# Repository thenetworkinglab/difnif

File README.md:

# DifNif: DBA-ESDI Solid State Drive Emulator

DifNif is a drive emulator that replaces an IBM DBA-ESDI hard drive. 
It was designed by Eric Schlaepfer ([schlae/difnif](https://github.com/schlae/difnif)),
with the project's initial release intended to replace the hard drive in 
IBM ThinkPad 700C laptops, also including an alpha version of a PS/2 desktop 
form-factor emulator.  This fork is an attempt to complete 
the development of the 72-pin board for PS/2 desktops; the changes are 
listed in [docs/formfactor-review.md](docs/formfactor-review.md).

And before you ask: the name 'DifNif' comes from DF9F, 
the Micro Channel adapter ID that IBM's DBA-ESDI drives report.

**Status: alpha.** See "Status" below before building anything.

## Background

IBM PS/2 computers from the late 1980s and early 1990s typically used a
disk interface called DBA-ESDI (Direct Bus Attach - Enhanced
Small Device Interface). A DBA-ESDI drive has its controller integrated
with the drive electronics, and sits directly on the Micro Channel
bus, more like an IDE drive, but with its own register interface.

These drives are becoming rare because many have failed mechanically or
been damaged by leaking capacitors. MCA SCSI cards are an alternative on some
machines, but are getting expensive and difficult to find as well and 
aren't compatible with all PS/2s. Some PS/2s also need an IML (initial microcode load)
partition on their disk, and can only load it from a DBA-ESDI drive.

DifNif uses a Teensy 4.1 microcontroller and a Lattice iCE40 FPGA to implement the
DBA-ESDI interface, and stores the disk as an image file on an SD card. 

## Two boards, one design

The boards share the FPGA design (`verilog/`) and the Teensy firmware
(`difnift/`), and differ in how they connect to the computer.

| | ThinkPad board | PS/2 desktop board |
|---|---|---|
| Folder | [pcb_thinkpad](pcb_thinkpad/) | [pcb_formfactor](pcb_formfactor/) |
| Machines | ThinkPad 700C | PS/2 desktops that take a 72-pin DBA-ESDI drive, such as the 50Z, 55SX and 70 |
| Connector | 2 mm header, wired to the flex cable taken from a stock 700-series 2.5" drive | 72-pin (2 x 36) card edge, plugging straight into the drive socket |
| Carrier | [mech/df9f_carrier.STL](mech/df9f_carrier.STL) | [mech/difnif_PS2_drive_sled.STL](mech/difnif_PS2_drive_sled.STL), replacing the IBM drive sled |
| FPGA build | `make` | `make BOARD=ps2` |

There are also debugging aids:

- [pcb_finglonger](pcb_finglonger/), the "Fing Longer", for the ThinkPad board.
  It fits a 3D-printed sled ([mech/finglong.STL](mech/finglong.STL)) held by two
  clips ([mech/2finglong.STL](mech/2finglong.STL)). One acts as an extender
  that brings the connector forward, and a second as a breakout for logic
  analyzer probes on the bus lines.
- For the 72-pin board, a card in a spare Micro Channel slot gives access to
  the bus signals; Eric used a spare
  [Snark Barker MCA](https://github.com/schlae/snark-barker-mca).

## Status

- **ThinkPad board:** Eric's board works in a ThinkPad 700C,
  running Windows 3.1. The FPGA design has since been changed in this fork (see
  [docs/formfactor-review.md](docs/formfactor-review.md)), and those changes
  have **not** been tested on a ThinkPad. Eric's original files are on the
  `main` branch.
- **PS/2 desktop board, Rev P1** (Eric's): register communication didn't work
  reliably in a 50Z.
- **PS/2 desktop board, Rev P2** (this fork): fixes the problems found in a
  review of Rev P1, including a floating reset input that is the likely cause
  of the 50Z problem. The fixes have been checked in simulation against IBM's
  bus timing, but **Rev P2 has not yet been built or tested on real hardware.**
- Both boards' original design powers the 74LVC4245A level shifters the wrong
  way round, putting 5V on a supply pin rated for 4.6V at most. Rev P2 uses
  the TI SN74LVC8T245 instead, which accepts 5V on either side and fits the
  same footprint. The same swap should work on the ThinkPad board but hasn't
  been tried.
- Known bugs: writes occasionally produce a sector shifted by one byte; the
  cause hasn't been found.

[docs/formfactor-review.md](docs/formfactor-review.md) has the full list of
findings and changes, and [docs/verify-findings.md](docs/verify-findings.md)
explains how to check each one against Eric's original files and IBM's
documents.

**Data loss:** this is a hobby project with no formal testing. Keep backup
copies of all disk images.

## Building

This is an advanced project. It needs surface-mount soldering (or an
assembly service), two programmable devices to load, and probably debugging
with an oscilloscope and a logic analyzer.

### Boards

Each board folder has a `fab/` folder with Gerber and drill files. For the
Rev P2 PS/2 board, `pcb_formfactor/fab/` also has a parts list
(`DifNifFormFactor-RevP2-BOM.csv`) and a placement file
(`DifNifFormFactor-RevP2-positions.csv`) for an assembly service. The
ordering notes in [docs/formfactor-review.md](docs/formfactor-review.md)
cover board thickness, gold fingers and the bevelled edge.

The Teensy 4.1 plugs into two 24-pin female header strips (2.54 mm pitch, rows
15.24 mm apart). The SD card goes in the Teensy's own card slot.

### Teensy firmware

Load [difnift/difnift.ino](difnift/difnift.ino) with the Arduino IDE and
PJRC's Teensy board support, selecting Teensy 4.1.

For register loopback testing with DIFDIAG, comment out the two lines at the
start of `loop()` that call `esdiReset()` and `mainLoop()`. The serial monitor
then accepts the single-letter test commands listed at startup.

### FPGA

The FPGA design is built with the open-source iCE40 tools (yosys, nextpnr and
icestorm, for example from
[oss-cad-suite](https://github.com/YosysHQ/oss-cad-suite-build)). In
`verilog/`:

    make                  # ThinkPad board
    make BOARD=ps2        # PS/2 desktop board

The PS/2 build turns on the POS registers, so the card reports its `DF9F`
ID. Each build goes into its own folder, `build/thinkpad/` or `build/ps2/`.

The FPGA loads its program from an SPI flash chip on the board, which is
written through header J2 with an FTDI FT232H or FT2232H adapter and
`iceprog`:

    make prog BOARD=ps2

| J2 pin | Signal | FT232H pin |
|---|---|---|
| 1 | Flash chip select | AD4 |
| 2 | CDONE | AD6 |
| 3 | SCK | AD0 |
| 4 | CRESET | AD7 |
| 5 | Flash data out (CIPO) | AD2 |
| 6 | GND | GND |
| 7 | Flash data in (COPI) | AD1 |
| 8 | +3.3 V (board supply, leave unconnected) | |

The board must be powered while programming. The Teensy's USB connection can
power it on the bench.

The source files are:

- `difnif_top.v`: top level, wiring up the other modules.
- `mcabus.v`: the Micro Channel bus interface, with the ESDI registers, POS
  registers and DMA.
- `teensy.v`: the register interface that lets the Teensy, in its own clock
  domain, reach the ESDI mailbox registers and flags.

The self-checking bus simulation for the PS/2 board is `difnif72_t.v`, run with
`./run_sim72.sh` (needs Icarus Verilog).

## Drive images

The Teensy firmware uses a file called `disk0.img` in the root of the SD card.
Its size must be a whole number of megabytes, up to 1023 MB; for example, for
120 MB:

    dd if=/dev/zero of=disk0.img bs=1048576 count=120

Then use the machine's reference disk to create the IML and reference
partitions, and install DOS to partition and format the rest of the disk.

## DIFDIAG

[difdiag/DIFDIAG.CPP](difdiag/DIFDIAG.CPP) is a diagnostic utility for
DBA-ESDI drives that works directly with the drive hardware at a very low
level. Don't use it on drives containing data you care about, but it can help
with troubleshooting dead drives. It compiles with Borland C++ using the Large
memory model.

Menus:

- **Settings:** DMA configuration. Autoconfigure tries to get the DMA channel
  through a BIOS call, and failing that from the extended BIOS data area
  (EBDA). The channel can also be set by hand, or PIO mode chosen instead.
- **Mailbox tests:** not for real drives. With DifNif in loopback test mode
  (see "Teensy firmware"), runs millions of register cycles to look for timing
  problems.
- **Low level commands:** the lowest-level commands, which must be run in the
  sequence given by the flowcharts in the
  [ESDI spec](https://ardent-tool.com/docs/pdf/j_mcspec.pdf).
- **Drive information:** query commands; generally safe on real drives.
- **POST tests:** modelled on the drive tests run by the PS/2 BIOS.
- **Run diagnostics:** the DBA-ESDI interface's own low-level hardware
  diagnostic command.
- **Int13 tests:** destructive. Writes data through the BIOS int13 routines,
  reads it back and compares.
- **Read sector:** reads one or more sectors and shows them in hex.

## Reference documents

- [IBM DBA-ESDI reference](https://ardent-tool.com/docs/pdf/j_mcspec.pdf)
- [DBA-ESDI 72-pin connector pinout](https://ardent-tool.com/storage/DBA_ESDI.html)
- [IBM PS/2 Hardware Interface Technical Reference, Micro Channel chapter](https://ardent-tool.com/docs/pdf/ps2_50-60_techref_ch2_microchannel_architecture.pdf)

## License

Designed by Eric Schlaepfer; modified in this fork by thenetworkinglab (2026).
Licensed under the
[CERN Open Hardware Licence Version 2 - Strongly Reciprocal](https://ohwr.org/cern_ohl_s_v2.txt).

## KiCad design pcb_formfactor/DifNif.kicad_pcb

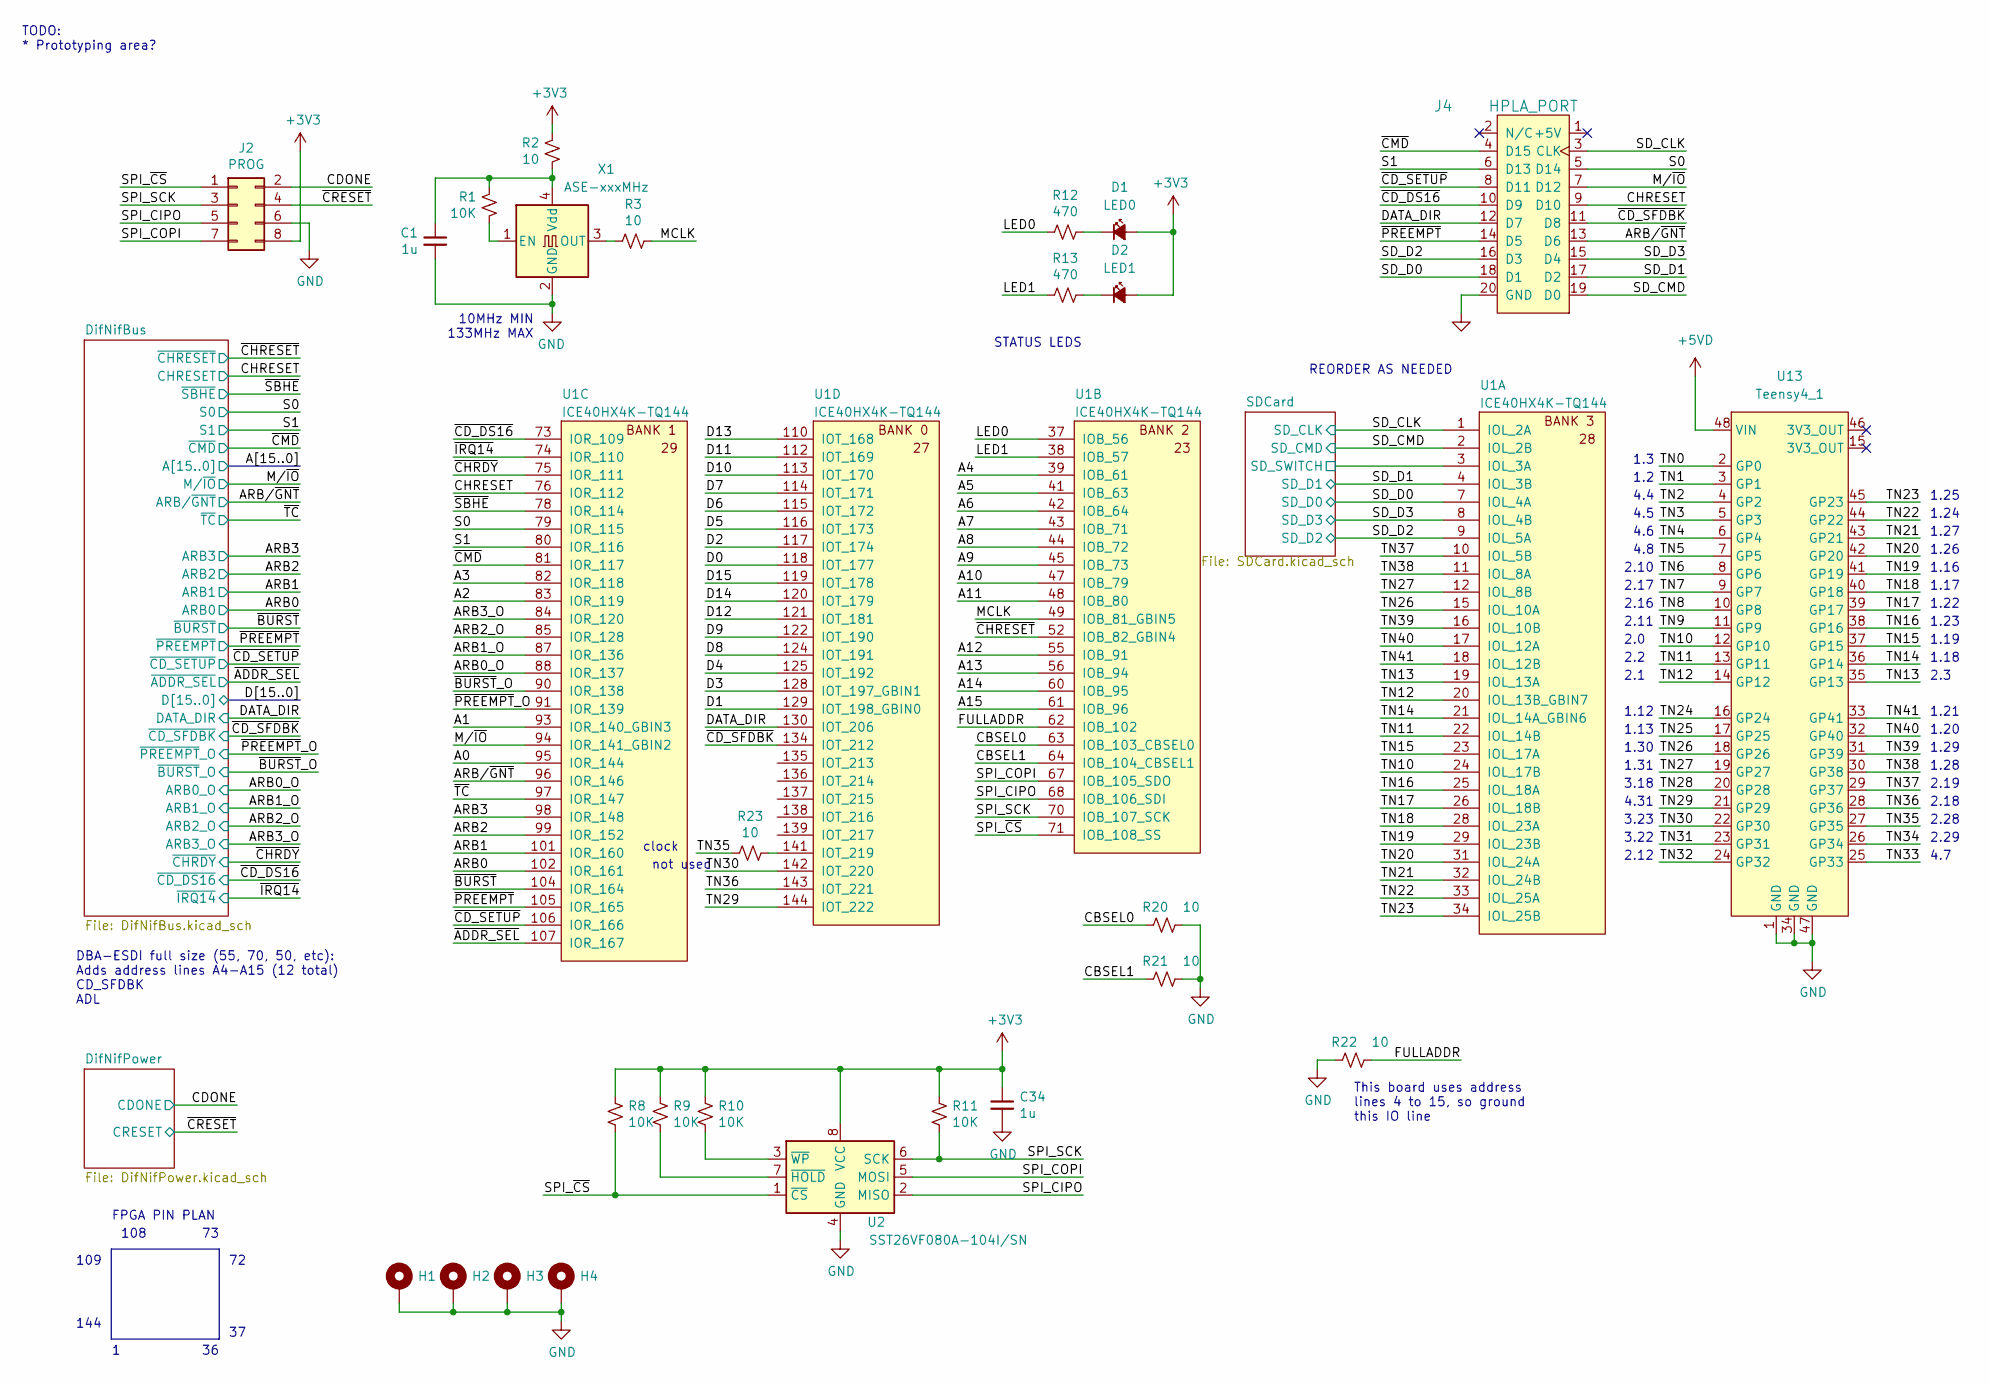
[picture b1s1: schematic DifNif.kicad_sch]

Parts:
C1, C34: 1u; CAPC1608X100; Mouser 810-CGA3E1X7R1C105AC
D1: LED0; LEDM1608X50
D2: LED1; LEDM1608X50
H1, H2, H3, H4: MountingHole_Pad; MountingHole_2.7mm_Pad
J2: PROG; PinHeader_2x04_P2.54mm_Vertical
J4: HPLA_PORT; PinHeader_2x10_P2.54mm_Vertical
R1, R8, R9, R10, R11: 10K; RESC1608X55; Mouser 603-RC0603FR-0710KL
R2, R3, R20, R21, R22, R23: 10; RESC1608X55; Mouser 603-RC0603FR-0710RL
R12, R13: 470; RESC1608X55; Mouser 603-RC0603FR-07470RL
U1: ICE40HX4K-TQ144; TSQFP50P2200X2200X160-144; Mouser 842-ICE40HX4K-TQ144
U2: SST26VF080A-104I/SN; SOP127P620X175-8; Mouser 579-26VF080A-104I/SN
U13: Teensy4_1; DIP-48_W15.24mm_Socket
X1: ASE-xxxMHz; XTAL320X250X120-4; Mouser 520-ECS-2333-100-BNT

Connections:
+3V3: C34.1, D1.2 (A), D2.2 (A), J2.8, R2.1, R8.1, R9.1, R10.1, R11.1, U2.8 (VCC); also elsewhere on the board
+5VD: U13.48 (VIN); also elsewhere on the board
/A0: U1.95 (IOR_144); also elsewhere on the board
/A1: U1.93 (IOR_140_GBIN3); also elsewhere on the board
/A2: U1.83 (IOR_119); also elsewhere on the board
/A3: U1.82 (IOR_118); also elsewhere on the board
/A4: U1.39 (IOB_61); also elsewhere on the board
/A5: U1.41 (IOB_63); also elsewhere on the board
/A6: U1.42 (IOB_64); also elsewhere on the board
/A7: U1.43 (IOB_71); also elsewhere on the board
/A8: U1.44 (IOB_72); also elsewhere on the board
/A9: U1.45 (IOB_73); also elsewhere on the board
/A10: U1.47 (IOB_79); also elsewhere on the board
/A11: U1.48 (IOB_80); also elsewhere on the board
/A12: U1.55 (IOB_91); also elsewhere on the board
/A13: U1.56 (IOB_94); also elsewhere on the board
/A14: U1.60 (IOB_95); also elsewhere on the board
/A15: U1.61 (IOB_96); also elsewhere on the board
/ARB0: U1.102 (IOR_161); also elsewhere on the board
/ARB0_O: U1.88 (IOR_137); also elsewhere on the board
/ARB1: U1.101 (IOR_160); also elsewhere on the board
/ARB1_O: U1.87 (IOR_136); also elsewhere on the board
/ARB2: U1.99 (IOR_152); also elsewhere on the board
/ARB2_O: U1.85 (IOR_128); also elsewhere on the board
/ARB3: U1.98 (IOR_148); also elsewhere on the board
/ARB3_O: U1.84 (IOR_120); also elsewhere on the board
/ARB/~GNT: J4.13 (D6), U1.96 (IOR_146); also elsewhere on the board
/CBSEL0: R20.2, U1.63 (IOB_103_CBSEL0)
/CBSEL1: R21.2, U1.64 (IOB_104_CBSEL1)
/CDONE: J2.2; also elsewhere on the board
/CHRESET: J4.9 (D10), U1.76 (IOR_112); also elsewhere on the board
/D0: U1.118 (IOT_177); also elsewhere on the board
/D1: U1.129 (IOT_198_GBIN0); also elsewhere on the board
/D2: U1.117 (IOT_174); also elsewhere on the board
/D3: U1.128 (IOT_197_GBIN1); also elsewhere on the board
/D4: U1.125 (IOT_192); also elsewhere on the board
/D5: U1.116 (IOT_173); also elsewhere on the board
/D6: U1.115 (IOT_172); also elsewhere on the board
/D7: U1.114 (IOT_171); also elsewhere on the board
/D8: U1.124 (IOT_191); also elsewhere on the board
/D9: U1.122 (IOT_190); also elsewhere on the board
/D10: U1.113 (IOT_170); also elsewhere on the board
/D11: U1.112 (IOT_169); also elsewhere on the board
/D12: U1.121 (IOT_181); also elsewhere on the board
/D13: U1.110 (IOT_168); also elsewhere on the board
/D14: U1.120 (IOT_179); also elsewhere on the board
/D15: U1.119 (IOT_178); also elsewhere on the board
/DATA_DIR: J4.12 (D7), U1.130 (IOT_206); also elsewhere on the board
/FULLADDR: R22.1, U1.62 (IOB_102)
/LED0: R12.2, U1.37 (IOB_56)
/LED1: R13.2, U1.38 (IOB_57)
/MCLK: R3.1, U1.49 (IOB_81_GBIN5)
/M/~IO: J4.7 (D12), U1.94 (IOR_141_GBIN2); also elsewhere on the board
/S0: J4.5 (D14), U1.79 (IOR_115); also elsewhere on the board
/S1: J4.6 (D13), U1.80 (IOR_116); also elsewhere on the board
/SDCard/SD_SWITCH: U1.3 (IOL_3A); also elsewhere on the board
/SD_CLK: J4.3 (CLK), U1.1 (IOL_2A); also elsewhere on the board
/SD_CMD: J4.19 (D0), U1.2 (IOL_2B); also elsewhere on the board
/SD_D0: J4.18 (D1), U1.7 (IOL_4A); also elsewhere on the board
/SD_D1: J4.17 (D2), U1.4 (IOL_3B); also elsewhere on the board
/SD_D2: J4.16 (D3), U1.9 (IOL_5A); also elsewhere on the board
/SD_D3: J4.15 (D4), U1.8 (IOL_4B); also elsewhere on the board
/SPI_CIPO: J2.5, U1.68 (IOB_106_SDI), U2.2 (MISO)
/SPI_COPI: J2.7, U1.67 (IOB_105_SDO), U2.5 (MOSI)
/SPI_SCK: J2.3, R11.2, U1.70 (IOB_107_SCK), U2.6 (SCK)
/SPI_~CS: J2.1, R8.2, U1.71 (IOB_108_SS), U2.1 (~CS)
/TN0: U13.2 (GP0)
/TN1: U13.3 (GP1)
/TN2: U13.4 (GP2)
/TN3: U13.5 (GP3)
/TN4: U13.6 (GP4)
/TN5: U13.7 (GP5)
/TN6: U13.8 (GP6)
/TN7: U13.9 (GP7)
/TN8: U13.10 (GP8)
/TN9: U13.11 (GP9)
/TN10: U1.24 (IOL_17B), U13.12 (GP10)
/TN11: U1.22 (IOL_14B), U13.13 (GP11)
/TN12: U1.20 (IOL_13B_GBIN7), U13.14 (GP12)
/TN13: U1.19 (IOL_13A), U13.35 (GP13)
/TN14: U1.21 (IOL_14A_GBIN6), U13.36 (GP14)
/TN15: U1.23 (IOL_17A), U13.37 (GP15)
/TN16: U1.25 (IOL_18A), U13.38 (GP16)
/TN17: U1.26 (IOL_18B), U13.39 (GP17)
/TN18: U1.28 (IOL_23A), U13.40 (GP18)
/TN19: U1.29 (IOL_23B), U13.41 (GP19)
/TN20: U1.31 (IOL_24A), U13.42 (GP20)
/TN21: U1.32 (IOL_24B), U13.43 (GP21)
/TN22: U1.33 (IOL_25A), U13.44 (GP22)
/TN23: U1.34 (IOL_25B), U13.45 (GP23)
/TN24: U13.16 (GP24)
/TN25: U13.17 (GP25)
/TN26: U1.15 (IOL_10A), U13.18 (GP26)
/TN27: U1.12 (IOL_8B), U13.19 (GP27)
/TN28: U13.20 (GP28)
/TN29: U1.144 (IOT_222), U13.21 (GP29)
/TN30: U1.142 (IOT_220), U13.22 (GP30)
/TN31: U13.23 (GP31)
/TN32: U13.24 (GP32)
/TN33: U13.25 (GP33)
/TN34: U13.26 (GP34)
/TN35: R23.2, U13.27 (GP35)
/TN36: U1.143 (IOT_221), U13.28 (GP36)
/TN37: U1.10 (IOL_5B), U13.29 (GP37)
/TN38: U1.11 (IOL_8A), U13.30 (GP38)
/TN39: U1.16 (IOL_10B), U13.31 (GP39)
/TN40: U1.17 (IOL_12A), U13.32 (GP40)
/TN41: U1.18 (IOL_12B), U13.33 (GP41)
/~ADDR_SEL: U1.107 (IOR_167)
/~BURST: U1.104 (IOR_164); also elsewhere on the board
/~BURST_O: U1.90 (IOR_138); also elsewhere on the board
/~CD_DS16: J4.10 (D9), U1.73 (IOR_109); also elsewhere on the board
/~CD_SETUP: J4.8 (D11), U1.106 (IOR_166); also elsewhere on the board
/~CD_SFDBK: J4.11 (D8), U1.134 (IOT_212); also elsewhere on the board
/~CHRDY: U1.75 (IOR_111); also elsewhere on the board
/~CHRESET: U1.52 (IOB_82_GBIN4); also elsewhere on the board
/~CMD: J4.4 (D15), U1.81 (IOR_117); also elsewhere on the board
/~CRESET: J2.4; also elsewhere on the board
/~IRQ14: U1.74 (IOR_110); also elsewhere on the board
/~PREEMPT: J4.14 (D5), U1.105 (IOR_165); also elsewhere on the board
/~PREEMPT_O: U1.91 (IOR_139); also elsewhere on the board
/~SBHE: U1.78 (IOR_114); also elsewhere on the board
/~TC: U1.97 (IOR_147); also elsewhere on the board
GND: C1.2, C34.2, H1.1, H2.1, H3.1, H4.1, J2.6, J4.20 (GND), R20.1, R21.1, R22.2, U2.4 (GND), U13.1 (GND), U13.34 (GND), U13.47 (GND), X1.2 (GND); also elsewhere on the board
unnamed: D1.1 (K), R12.1
unnamed: D2.1 (K), R13.1
unnamed: R23.1, U1.141 (IOT_219)
unnamed: R9.2, U2.7 (~HOLD)
unnamed: R10.2, U2.3 (~WP)
unnamed: R1.2, X1.1 (EN)
unnamed: R3.2, X1.3 (OUT)
unnamed: C1.1, R1.1, R2.2, X1.4 (Vdd)

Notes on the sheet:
2.1
2.19
4.31
1.16
2.17
2.18
1.30
2.16
1.27
clock
1.2
REORDER AS NEEDED
2.3
2.0
3.22
STATUS LEDS
TODO: * Prototyping area?
4.7
1.31
1.21
2.28
1.24
1.29
1.19
4.6
2.12
2.10
3.18
1.17
3.23
1.3
1.25
4.5
1.20
2.29
2.11
4.4
1.18
1.28
2.2

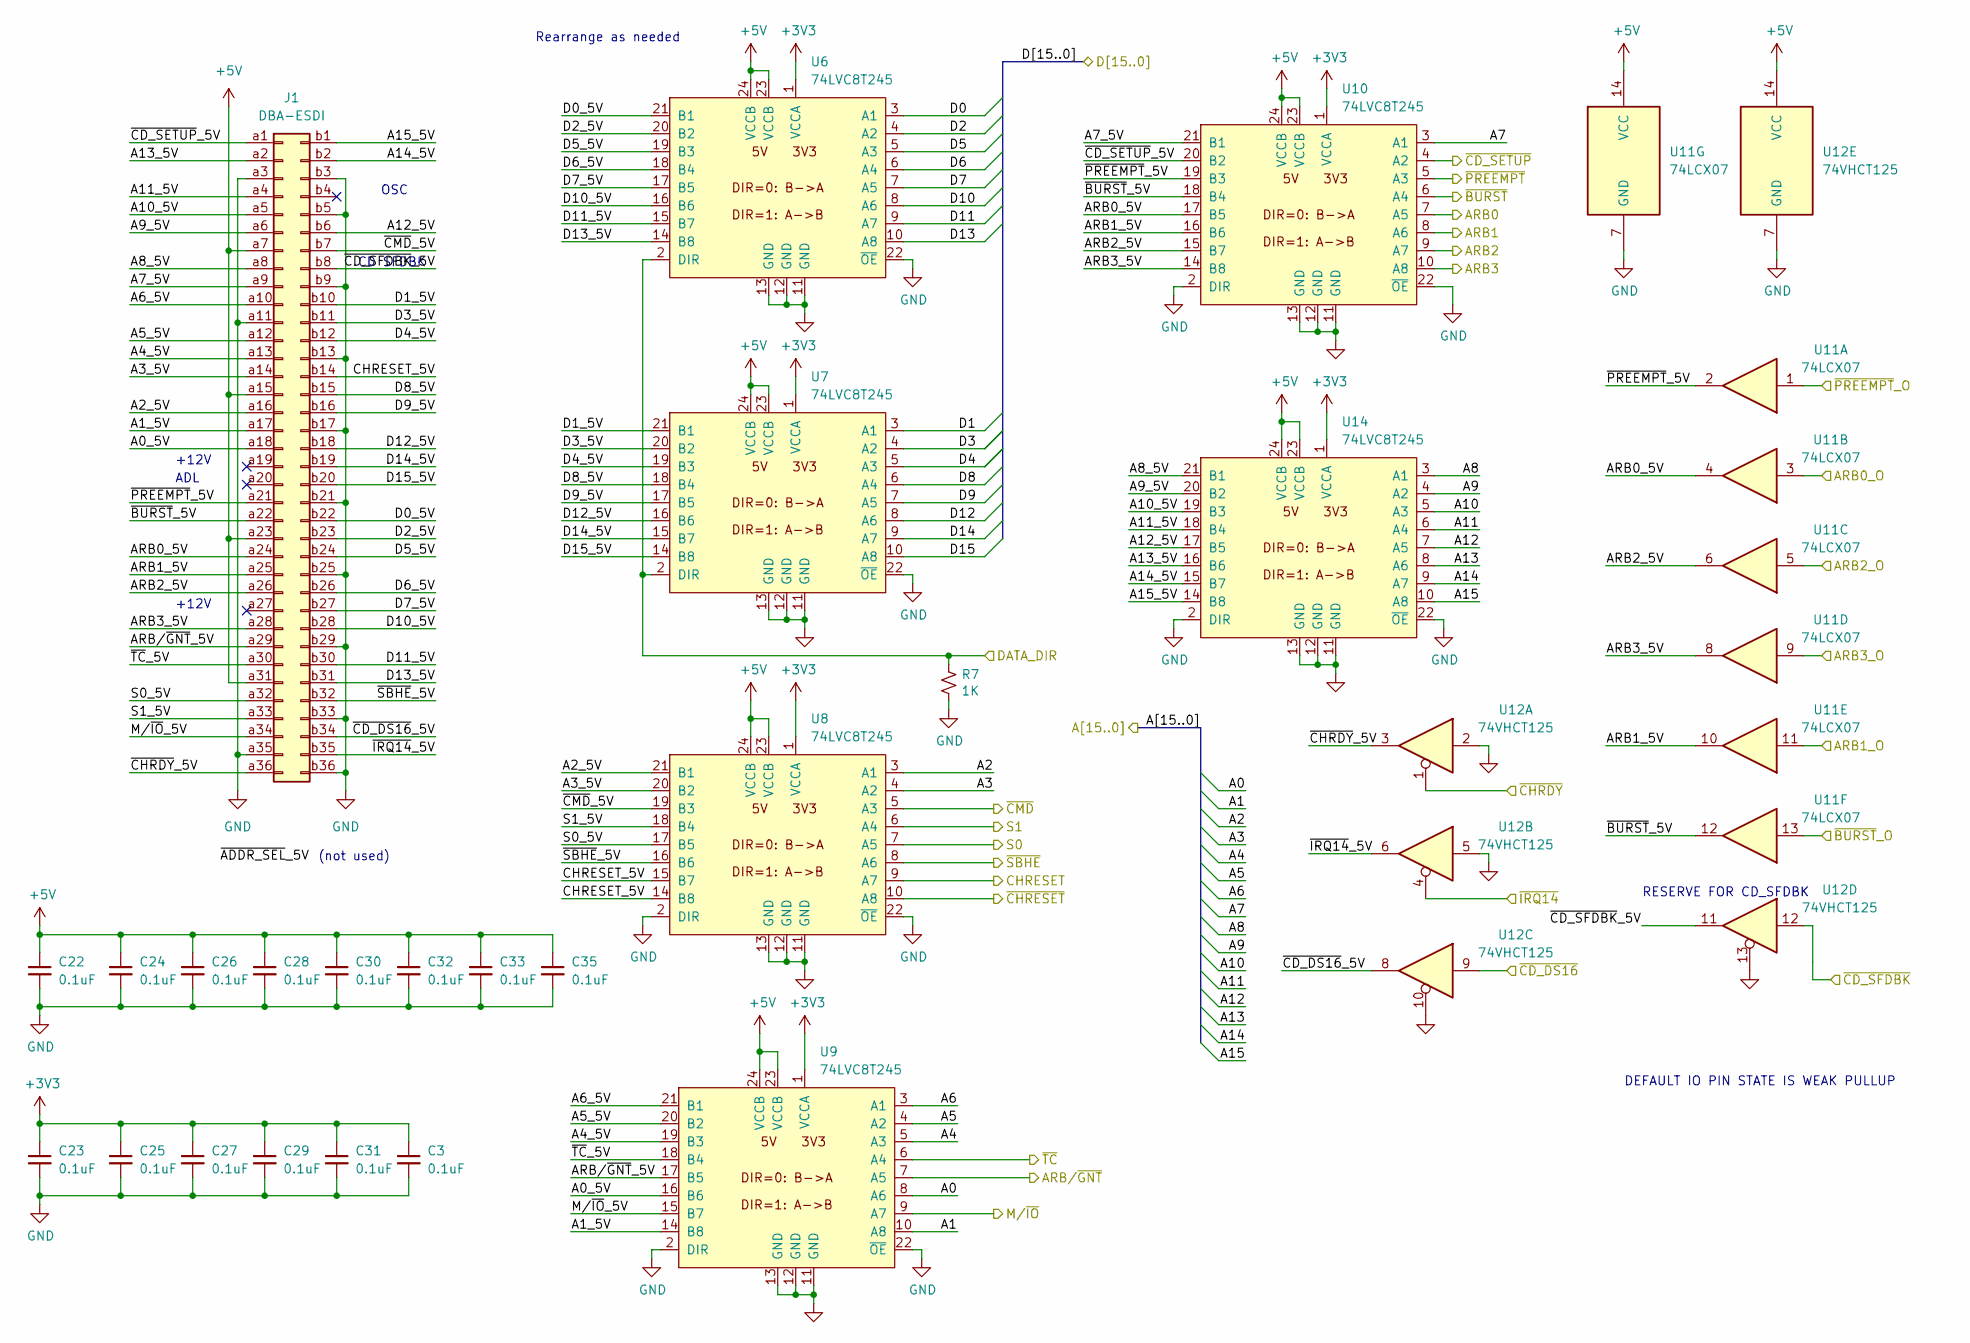
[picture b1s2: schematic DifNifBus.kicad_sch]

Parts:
C3, C22, C23, C24, C25, C26, C27, C28, C29, C30, C31, C32, C33, C35: 0.1uF; CAPC1608X100
J1: DBA-ESDI; BUS_DBA_ESDI
R7: 1K; RESC1608X55; Mouser 603-RC0603FR-071KL
U6, U7, U8, U9, U10, U14: 74LVC8T245; TSOP65P640X120-24; Mouser 595-SN74LVC8T245PWR
U11: 74LCX07; TSOP65P640X110-14; Mouser 757-74LCX07FTAE
U12: 74VHCT125; TSOP65P640X110-14; Mouser 757-74VHCT125AFT

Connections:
+3V3: C3.1, C23.1, C25.1, C27.1, C29.1, C31.1, U6.1 (VCCA), U7.1 (VCCA), U8.1 (VCCA), U9.1 (VCCA), U10.1 (VCCA), U14.1 (VCCA); also elsewhere on the board
+5V: C22.1, C24.1, C26.1, C28.1, C30.1, C32.1, C33.1, C35.1, J1.a7, J1.a15, J1.a23, J1.a31, U6.23 (VCCB), U6.24 (VCCB), U7.23 (VCCB), U7.24 (VCCB), U8.23 (VCCB), U8.24 (VCCB), U9.23 (VCCB), U9.24 (VCCB), U10.23 (VCCB), U10.24 (VCCB), U11.14 (VCC), U12.14 (VCC), U14.23 (VCCB), U14.24 (VCCB); also elsewhere on the board
/A0: U9.8 (A5); also elsewhere on the board
/A1: U9.10 (A7); also elsewhere on the board
/A2: U8.3 (A0); also elsewhere on the board
/A3: U8.4 (A1); also elsewhere on the board
/A4: U9.5 (A2); also elsewhere on the board
/A5: U9.4 (A1); also elsewhere on the board
/A6: U9.3 (A0); also elsewhere on the board
/A7: U10.3 (A0); also elsewhere on the board
/A8: U14.3 (A0); also elsewhere on the board
/A9: U14.4 (A1); also elsewhere on the board
/A10: U14.5 (A2); also elsewhere on the board
/A11: U14.6 (A3); also elsewhere on the board
/A12: U14.7 (A4); also elsewhere on the board
/A13: U14.8 (A5); also elsewhere on the board
/A14: U14.9 (A6); also elsewhere on the board
/A15: U14.10 (A7); also elsewhere on the board
/ARB0: U10.7 (A4); also elsewhere on the board
/ARB0_O: U11.3; also elsewhere on the board
/ARB1: U10.8 (A5); also elsewhere on the board
/ARB1_O: U11.11; also elsewhere on the board
/ARB2: U10.9 (A6); also elsewhere on the board
/ARB2_O: U11.5; also elsewhere on the board
/ARB3: U10.10 (A7); also elsewhere on the board
/ARB3_O: U11.9; also elsewhere on the board
/ARB/~GNT: U9.7 (A4); also elsewhere on the board
/CHRESET: U8.9 (A6); also elsewhere on the board
/D0: U6.3 (A0); also elsewhere on the board
/D1: U7.3 (A0); also elsewhere on the board
/D2: U6.4 (A1); also elsewhere on the board
/D3: U7.4 (A1); also elsewhere on the board
/D4: U7.5 (A2); also elsewhere on the board
/D5: U6.5 (A2); also elsewhere on the board
/D6: U6.6 (A3); also elsewhere on the board
/D7: U6.7 (A4); also elsewhere on the board
/D8: U7.6 (A3); also elsewhere on the board
/D9: U7.7 (A4); also elsewhere on the board
/D10: U6.8 (A5); also elsewhere on the board
/D11: U6.9 (A6); also elsewhere on the board
/D12: U7.8 (A5); also elsewhere on the board
/D13: U6.10 (A7); also elsewhere on the board
/D14: U7.9 (A6); also elsewhere on the board
/D15: U7.10 (A7); also elsewhere on the board
/DATA_DIR: R7.1, U6.2 (DIR), U7.2 (DIR); also elsewhere on the board
/DifNifBus/A0_5V: J1.a18, U9.16 (B5)
/DifNifBus/A1_5V: J1.a17, U9.14 (B7)
/DifNifBus/A2_5V: J1.a16, U8.21 (B0)
/DifNifBus/A3_5V: J1.a14, U8.20 (B1)
/DifNifBus/A4_5V: J1.a13, U9.19 (B2)
/DifNifBus/A5_5V: J1.a12, U9.20 (B1)
/DifNifBus/A6_5V: J1.a10, U9.21 (B0)
/DifNifBus/A7_5V: J1.a9, U10.21 (B0)
/DifNifBus/A8_5V: J1.a8, U14.21 (B0)
/DifNifBus/A9_5V: J1.a6, U14.20 (B1)
/DifNifBus/A10_5V: J1.a5, U14.19 (B2)
/DifNifBus/A11_5V: J1.a4, U14.18 (B3)
/DifNifBus/A12_5V: J1.b6, U14.17 (B4)
/DifNifBus/A13_5V: J1.a2, U14.16 (B5)
/DifNifBus/A14_5V: J1.b2, U14.15 (B6)
/DifNifBus/A15_5V: J1.b1, U14.14 (B7)
/DifNifBus/ARB0_5V: J1.a24, U10.17 (B4), U11.4
/DifNifBus/ARB1_5V: J1.a25, U10.16 (B5), U11.10
/DifNifBus/ARB2_5V: J1.a26, U10.15 (B6), U11.6
/DifNifBus/ARB3_5V: J1.a28, U10.14 (B7), U11.8
/DifNifBus/ARB/~GNT_5V: J1.a29, U9.17 (B4)
/DifNifBus/CHRESET_5V: J1.b14, U8.14 (B7), U8.15 (B6)
/DifNifBus/D0_5V: J1.b22, U6.21 (B0)
/DifNifBus/D1_5V: J1.b10, U7.21 (B0)
/DifNifBus/D2_5V: J1.b23, U6.20 (B1)
/DifNifBus/D3_5V: J1.b11, U7.20 (B1)
/DifNifBus/D4_5V: J1.b12, U7.19 (B2)
/DifNifBus/D5_5V: J1.b24, U6.19 (B2)
/DifNifBus/D6_5V: J1.b26, U6.18 (B3)
/DifNifBus/D7_5V: J1.b27, U6.17 (B4)
/DifNifBus/D8_5V: J1.b15, U7.18 (B3)
/DifNifBus/D9_5V: J1.b16, U7.17 (B4)
/DifNifBus/D10_5V: J1.b28, U6.16 (B5)
/DifNifBus/D11_5V: J1.b30, U6.15 (B6)
/DifNifBus/D12_5V: J1.b18, U7.16 (B5)
/DifNifBus/D13_5V: J1.b31, U6.14 (B7)
/DifNifBus/D14_5V: J1.b19, U7.15 (B6)
/DifNifBus/D15_5V: J1.b20, U7.14 (B7)
/DifNifBus/M/~IO_5V: J1.a34, U9.15 (B6)
/DifNifBus/S0_5V: J1.a32, U8.17 (B4)
/DifNifBus/S1_5V: J1.a33, U8.18 (B3)
/DifNifBus/~BURST_5V: J1.a22, U10.18 (B3), U11.12
/DifNifBus/~CD_DS16_5V: J1.b34, U12.8
/DifNifBus/~CD_SETUP_5V: J1.a1, U10.20 (B1)
/DifNifBus/~CD_SFDBK_5V: J1.b8, U12.11
/DifNifBus/~CHRDY_5V: J1.a36, U12.3
/DifNifBus/~CMD_5V: J1.b7, U8.19 (B2)
/DifNifBus/~IRQ14_5V: J1.b35, U12.6
/DifNifBus/~PREEMPT_5V: J1.a21, U10.19 (B2), U11.2
/DifNifBus/~SBHE_5V: J1.b32, U8.16 (B5)
/DifNifBus/~TC_5V: J1.a30, U9.18 (B3)
/M/~IO: U9.9 (A6); also elsewhere on the board
/S0: U8.7 (A4); also elsewhere on the board
/S1: U8.6 (A3); also elsewhere on the board
/~BURST: U10.6 (A3); also elsewhere on the board
/~BURST_O: U11.13; also elsewhere on the board
/~CD_DS16: U12.9; also elsewhere on the board
/~CD_SETUP: U10.4 (A1); also elsewhere on the board
/~CD_SFDBK: U12.12; also elsewhere on the board
/~CHRDY: U12.1; also elsewhere on the board
/~CHRESET: U8.10 (A7); also elsewhere on the board
/~CMD: U8.5 (A2); also elsewhere on the board
/~IRQ14: U12.4; also elsewhere on the board
/~PREEMPT: U10.5 (A2); also elsewhere on the board
/~PREEMPT_O: U11.1; also elsewhere on the board
/~SBHE: U8.8 (A5); also elsewhere on the board
/~TC: U9.6 (A3); also elsewhere on the board
GND: C3.2, C22.2, C23.2, C24.2, C25.2, C26.2, C27.2, C28.2, C29.2, C30.2, C31.2, C32.2, C33.2, C35.2, J1.a3, J1.a11, J1.a35, J1.b3, J1.b5, J1.b9, J1.b13, J1.b17, J1.b21, J1.b25, J1.b29, J1.b33, J1.b36, R7.2, U6.11 (GND), U6.12 (GND), U6.13 (GND), U6.22 (~OE), U7.11 (GND), U7.12 (GND), U7.13 (GND), U7.22 (~OE), U8.2 (DIR), U8.11 (GND), U8.12 (GND), U8.13 (GND), U8.22 (~OE), U9.2 (DIR), U9.11 (GND), U9.12 (GND), U9.13 (GND), U9.22 (~OE), U10.2 (DIR), U10.11 (GND), U10.12 (GND), U10.13 (GND), U10.22 (~OE), U11.7 (GND), U12.2, U12.5, U12.7 (GND), U12.10, U12.13, U14.2 (DIR), U14.11 (GND), U14.12 (GND), U14.13 (GND), U14.22 (~OE); also elsewhere on the board

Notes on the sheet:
Rearrange as needed
RESERVE FOR CD_SFDBK
+12V
(not used)
ADL
DEFAULT IO PIN STATE IS WEAK PULLUP
OSC
CD SFDBK

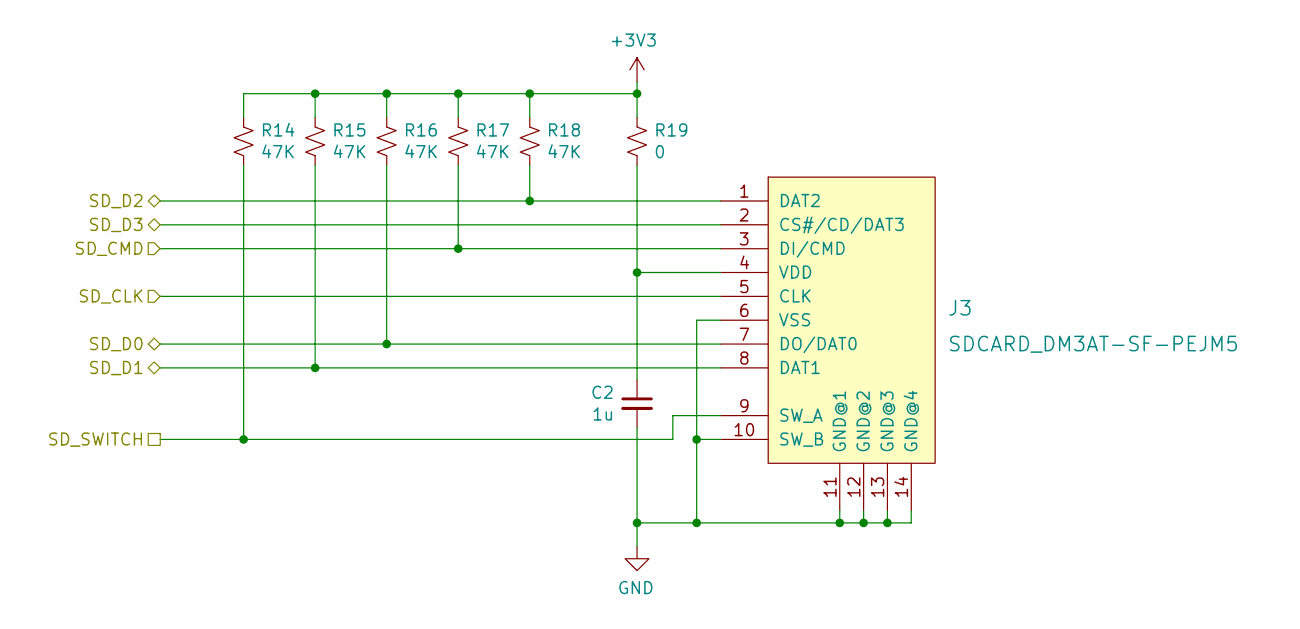
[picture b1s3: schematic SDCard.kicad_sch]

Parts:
C2: 1u; CAPC1608X100; Mouser 810-CGA3E1X7R1C105AC
J3: SDCARD_DM3AT-SF-PEJM5; microSD_HC_Hirose_DM3AT-SF-PEJM5; Mouser 798-DM3AT-SF-PEJM540
R14, R15, R16, R17, R18: 47K; RESC1608X55; Mouser 603-RC0603FR-0747KL
R19: 0; RESC2012X55; Mouser 603-RC0805FR-070RL

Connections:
+3V3: R14.1, R15.1, R16.1, R17.1, R18.1, R19.1; also elsewhere on the board
/SDCard/SD_SWITCH: J3.9 (SW_A), R14.2; also elsewhere on the board
/SD_CLK: J3.5 (CLK); also elsewhere on the board
/SD_CMD: J3.3 (DI/CMD), R17.2; also elsewhere on the board
/SD_D0: J3.7 (DO/DAT0), R16.2; also elsewhere on the board
/SD_D1: J3.8 (DAT1), R15.2; also elsewhere on the board
/SD_D2: J3.1 (DAT2), R18.2; also elsewhere on the board
/SD_D3: J3.2 (CS#/CD/DAT3); also elsewhere on the board
GND: C2.2, J3.6 (VSS), J3.10 (SW_B), J3.11 (GND@1), J3.12 (GND@2), J3.13 (GND@3), J3.14 (GND@4); also elsewhere on the board
unnamed: C2.1, J3.4 (VDD), R19.2

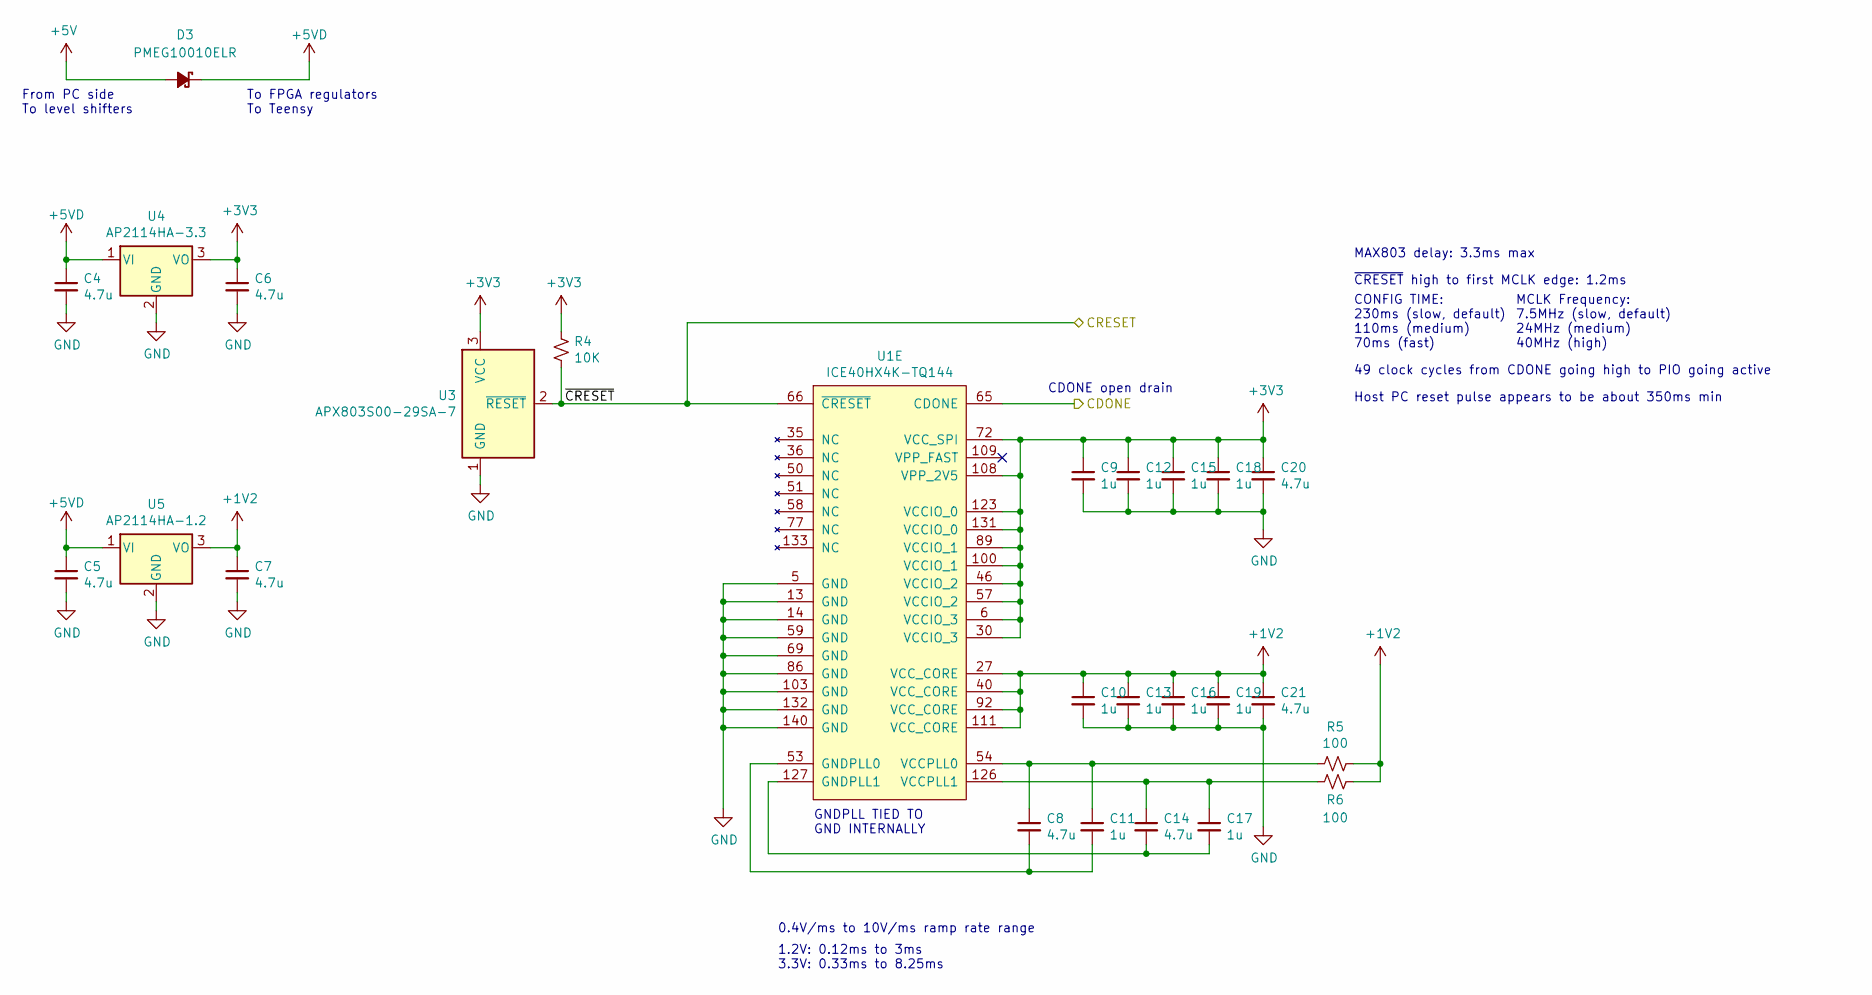
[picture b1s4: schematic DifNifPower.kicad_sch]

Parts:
C4, C5, C6, C7, C8, C14, C20, C21: 4.7u; CAPC1608X100; Mouser 187-CL10A475KP8NNNC
C9, C10, C11, C12, C13, C15, C16, C17, C18, C19: 1u; CAPC1608X100; Mouser 810-CGA3E1X7R1C105AC
D3: PMEG10010ELR; SOD3716X117; Mouser 771-PMEG10010ELRX
R4: 10K; RESC1608X55; Mouser 603-RC0603FR-0710KL
R5, R6: 100; RESC1608X55; Mouser 603-RC0603FR-07100RL
U1: ICE40HX4K-TQ144; TSQFP50P2200X2200X160-144; Mouser 842-ICE40HX4K-TQ144
U3: APX803S00-29SA-7; SOT95P230X117-3; Mouser 621-APX803S00-29SA-7
U4: AP2114HA-3.3; SOT230P700X170-3; Mouser 621-AP2114HA-3.3TRG1
U5: AP2114HA-1.2; SOT230P700X170-3; Mouser 621-AP2114HA-1.2TRG1

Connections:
+1V2: C7.1, C10.1, C13.1, C16.1, C19.1, C21.1, R5.1, R6.1, U1.27 (VCC_CORE), U1.40 (VCC_CORE), U1.92 (VCC_CORE), U1.111 (VCC_CORE), U5.3 (VO)
+3V3: C6.1, C9.1, C12.1, C15.1, C18.1, C20.1, R4.1, U1.6 (VCCIO_3), U1.30 (VCCIO_3), U1.46 (VCCIO_2), U1.57 (VCCIO_2), U1.72 (VCC_SPI), U1.89 (VCCIO_1), U1.100 (VCCIO_1), U1.108 (VPP_2V5), U1.123 (VCCIO_0), U1.131 (VCCIO_0), U3.3 (VCC), U4.3 (VO); also elsewhere on the board
+5V: D3.2 (A); also elsewhere on the board
+5VD: C4.1, C5.1, D3.1 (K), U4.1 (VI), U5.1 (VI); also elsewhere on the board
/CDONE: U1.65 (CDONE); also elsewhere on the board
/~CRESET: R4.2, U1.66 (~CRESET), U3.2 (~RESET); also elsewhere on the board
GND: C4.2, C5.2, C6.2, C7.2, C9.2, C10.2, C12.2, C13.2, C15.2, C16.2, C18.2, C19.2, C20.2, C21.2, U1.5 (GND), U1.13 (GND), U1.14 (GND), U1.59 (GND), U1.69 (GND), U1.86 (GND), U1.103 (GND), U1.132 (GND), U1.140 (GND), U3.1 (GND), U4.2 (GND), U5.2 (GND); also elsewhere on the board
unnamed: C8.2, C11.2, U1.53 (GNDPLL0)
unnamed: C14.2, C17.2, U1.127 (GNDPLL1)
unnamed: C8.1, C11.1, R5.2, U1.54 (VCCPLL0)
unnamed: C14.1, C17.1, R6.2, U1.126 (VCCPLL1)

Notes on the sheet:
49 clock cycles from CDONE going high to PIO going active
Host PC reset pulse appears to be about 350ms min
To FPGA regulators To Teensy
CONFIG TIME: 230ms (slow, default) 110ms (medium) 70ms (fast)
MCLK Frequency: 7.5MHz (slow, default) 24MHz (medium) 40MHz (high)
CDONE open drain
GNDPLL TIED TO GND INTERNALLY
From PC side To level shifters
0.4V/ms to 10V/ms ramp rate range
1.2V: 0.12ms to 3ms 3.3V: 0.33ms to 8.25ms
~{CRESET} high to first MCLK edge: 1.2ms
MAX803 delay: 3.3ms max

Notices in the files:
pcb_finglonger/700CExtender.kicad_pcb:
© 2023 TUBE TIME
